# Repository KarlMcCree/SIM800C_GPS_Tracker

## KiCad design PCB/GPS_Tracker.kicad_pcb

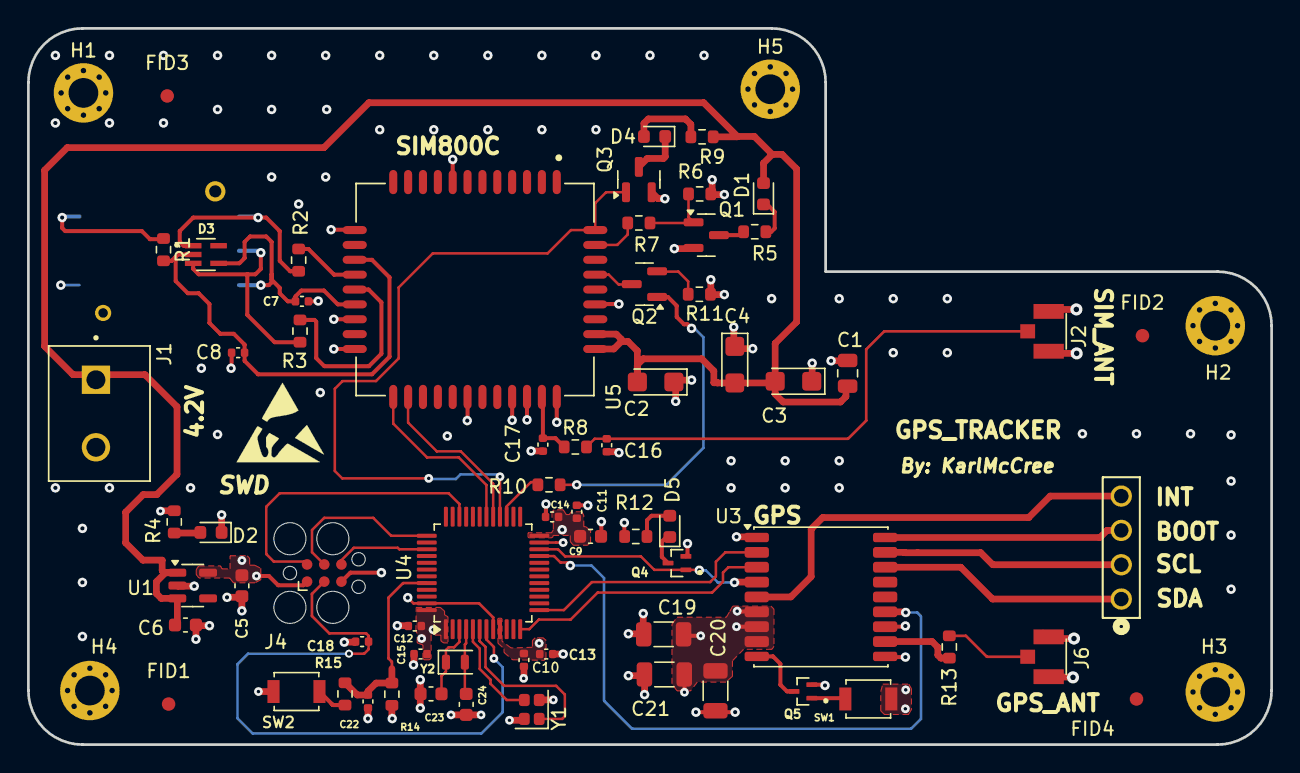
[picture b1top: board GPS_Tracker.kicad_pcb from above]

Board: 4 copper layers, 92.0 x 53.0 mm, 72 parts (1 on the bottom side), 49 nets.

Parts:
C1: 4u7; C_0805_2012Metric
C2, C3, C4: 100u; CP_EIA-3216-12_Kemet-S
C5, C6, C9: 4u7; C_0603_1608Metric
C7: 10n; C_0402_1005Metric
C8: 1n; C_0402_1005Metric
C10, C11, C12, C13, C14, C15, C18, C22: 100n; C_0402_1005Metric
C16, C17: 100p; C_0402_1005Metric
C19: 47u; C_1206_3216Metric
C20: 0u1; C_1206_3216Metric
C21: 10u; C_1206_3216Metric
C23, C24: 10p; C_0603_1608Metric
D1, D2, D4, D5: LED; LED_0603_1608Metric
D3: ESDA6V1W5; SOT65P210X110-5N
FID1, FID2, FID3, FID4: Fiducial; Fiducial_1mm_Mask3mm
H1, H2, H3, H4, H5: MountingHole_Pad; MountingHole_2.2mm_M2_Pad_Via
J1: BATT I/P; HANDSON_KF301-2P
J2, J6: U.FL-R-SMT_01_; HRS_U.FL-R-SMT_01_
J3: Conn_Socket; CONN_SD-42375-001_M295_04_MOL
J4: Conn_ARM_SWD_TagConnect_TC2030; Tag-Connect_TC2030-IDC-FP_2x03_P1.27mm_Vertical
J5: SIM8051-6-0-14-01-X-REVD; GCT_SIM8051-6-0-14-01-X-REVD
Q1, Q2, Q3: BC817; SOT-23
Q4, Q5: DTC143ZEBTL; SOTFL50P160X85-3N
R1, R2, R3: 27; R_0603_1608Metric
R4: 1k; R_0603_1608Metric
R5, R6: 47k; R_0603_1608Metric
R7, R13: 10k; R_0603_1608Metric
R8: 0R; R_0603_1608Metric
R9, R10, R11: 4k7; R_0603_1608Metric
R12: 2k2; R_0603_1608Metric
R14, R15: 5k1; R_0603_1608Metric
SW1, SW2: SW_Push; SW_SPST_B3U-1000P
U1: MIC5504-2.8YM5; TSOT-23-5
U3: MAX-8Q; ublox_MAX
U4: STM32F030C8Tx; LQFP-48_7x7mm_P0.5mm
U5: SIM800C; LCC110P1570X1760X250-42N
Y1: 8MHz; Crystal_SMD_2016-4Pin_2.0x1.6mm
Y2: 32Hz768; Crystal_SMD_2012-2Pin_2.0x1.2mm

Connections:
+2V8: C5.1, C9.1, C10.1, C11.1, C12.1, C13.1, C14.1, C15.1, C19.2, C20.2, C21.2, J4.1 (VCC), R4.2, R12.2, SW1.2, SW2.1, U1.5 (VOUT), U3.6 (V_BCKP), U3.7 (VCC_IO), U3.8 (VCC), U4.1 (VDD), U4.9 (VDDA), U4.24 (VDD), U4.48 (VDD)
+4V2: C1.2, C2.2, C3.2, C4.2, C6.1, D1.2 (A), J1.1, R9.1, U1.1 (VIN), U1.3 (EN), U5.34 (VBAT), U5.35 (VBAT)
/BOOT: J3.3, U3.18 (~SAFEBOOT)
/BOOT0: C22.1, R14.1, R15.2, U4.44 (BOOT0)
/GPS_EN: U3.13 (LNA_EN), U4.21 (PB10)
/GPS_PPS: Q4.1, U3.4 (TIMEPULSE), U4.22 (PB11)
/GPS_RF_IN: R13.2, U3.11 (RF_IN)
/GPS_RXD: U3.3 (RXD), U4.12 (PA2)
/GPS_TXD: U3.2 (TXD), U4.13 (PA3)
/HSE_IN: U4.5 (PF0), Y1.3
/HSE_OUT: U4.6 (PF1), Y1.1
/INT: J3.4, U3.5 (EXTINT)
/LED_GPS: D5.1 (K), Q4.3
/LED_GSM: D4.1 (K), Q3.3 (C)
/LED_PWR: D2.2 (A), R4.1
/LSE_IN: C23.1, U4.3 (PC14), Y2.1
/LSE_OUT: C24.1, U4.4 (PC15), Y2.2
/PWRKEY: Q2.3 (C), U5.39 (PWRKEY)
/RST: Q5.3, U3.9 (~RESET)
/SCL: J3.2, U3.17 (SCL)
/SDA: J3.1, U3.16 (SDA)
/SIM8_PWRKEY: R10.1, U4.27 (PB14)
/SIM8_RXD: U4.29 (PA8), U5.23 (UART2_RXD)
/SIM8_TXD: U4.30 (PA9), U5.22 (UART2_TXD)
/SIM_CLK: D3.1, J5.C3 (CLK), R2.2
/SIM_DATA: C8.1, D3.2, J5.C7 (I/O), R1.1, R1.2, U5.15 (SIM_DATA)
/SIM_NETLIGHT: R7.2, U5.41 (NETLIGHT)
/SIM_RST: D3.3, J5.C2 (RST), R3.2
/SIM_STATUS: Q3.1 (B), U4.28 (PB15), U5.42 (STATUS)
/SWD_CLK: J4.4 (SWCLK), U4.37 (PA14)
/SWD_DIO: J4.2 (SWDIO), U4.34 (PA13)
/SWD_NRST: C18.1, J4.3 (~RESET), U4.7 (NRST)
/SWD_TRC: J4.6 (SWO), U4.39 (PB3)
GND: C1.1, C2.1, C3.1, C4.1, C5.2, C6.2, C7.2, C8.2, C9.2, C10.2, C11.2, C12.2, C13.2, C14.2, C15.2, C16.2, C17.2, C18.2, C19.1, C20.1, C21.1, C22.2, C23.2, C24.2, D2.1 (K), H1.1, H2.1, H3.1, H4.1, H5.1, J1.2, J2.1 (GND), J2.2 (GND), J4.5 (GND), J5.C5 (GND), J6.1 (GND), J6.2 (GND), Q1.2 (E), Q3.2 (E), Q4.2, Q5.2, R6.1, R11.1, R14.2, U1.2 (GND), U3.1 (GND), U3.10 (GND), U3.12 (GND), U4.8 (VSSA), U4.23 (VSS), U4.47 (VSS), U5.8 (GND), U5.13 (GND), U5.19 (GND), U5.21 (GND), U5.27 (GND), U5.30 (GND), U5.31 (GND), U5.33 (GND), U5.36 (GND), U5.37 (GND), Y1.2, Y1.4
unnamed: D1.1 (K), R5.2
unnamed: D4.2 (A), R9.2
unnamed: D5.2 (A), R12.1
unnamed: C16.1, J2.3 (SIG), R8.2
unnamed: C7.1, D3.4, J5.C1 (VCC), U5.18 (SIM_VDD)
unnamed: J6.3 (SIG), R13.1
unnamed: Q1.1 (B), R6.2, R7.1
unnamed: Q1.3 (C), R5.1
unnamed: Q2.1 (B), R10.2
unnamed: Q2.2 (E), R11.2
unnamed: Q5.1, SW1.1
unnamed: R15.1, SW2.2
unnamed: C17.1, R8.1, U5.32 (GSM_ANT)
unnamed: R2.1, U5.16 (SIM_CLK)
unnamed: R3.1, U5.17 (SIM_RST)
